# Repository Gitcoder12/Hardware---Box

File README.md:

Hardware-Box

Universal Hardware Configuration, Cloning & Replication Platform

A comprehensive library of hardware and PCB configurations, with cloning, duplication, and replication capabilities using 3D printers and other suitable manufacturing technologies.

---

Overview

Hardware-Box aims to create a centralized ecosystem for documenting, analyzing, reconstructing, and replicating physical hardware.

The platform will organize hardware configurations, PCB layouts, electronic components, mechanical structures, CAD models, firmware documentation, and manufacturing specifications.

The long-term vision is to make hardware designs easier to understand, reproduce, modify, and manufacture.

Core Capabilities

- Hardware Database: Organized configurations for phones, televisions, computers, appliances, and electronic devices.
- PCB Library: Circuit board layouts, schematics, component placements, and board specifications.
- Hardware Cloning: Reconstruct compatible hardware designs from verified documentation and authorized reference devices.
- 3D Replication: Generate and reproduce compatible physical components using 3D printing.
- CAD Integration: Store and process STEP, STL, 3MF, and other supported design formats.
- Component Library: Catalog electronic and mechanical components with specifications.
- Manufacturing Support: Document suitable fabrication technologies, materials, tolerances, and assembly procedures.
- Compatibility Analysis: Compare hardware configurations and identify compatible replacement components.

Supported Hardware Categories

Category| Examples
Mobile Devices| Smartphones, tablets
Entertainment| Televisions, remotes, speakers
Computing| Laptops, desktops, accessories
Electronics| PCBs, embedded systems, controllers
Mechanical| Enclosures, brackets, connectors
Appliances| Electronic and mechanical components

Replication Technologies

- FDM / FFF 3D printing
- SLA / Resin printing
- SLS printing
- CNC machining
- PCB manufacturing
- Laser cutting
- Other suitable fabrication technologies

Not every component can be reproduced using 3D printing. Electronic chips, displays, sensors, and specialized components may require separate manufacturing or sourcing.

Planned Architecture

Hardware-Box/
│
├── database/
│   ├── devices/
│   ├── configurations/
│   └── manufacturers/
│
├── pcb/
│   ├── layouts/
│   ├── schematics/
│   └── components/
│
├── designs/
│   ├── cad/
│   ├── 3d-models/
│   └── mechanical/
│
├── fabrication/
│   ├── materials/
│   ├── printers/
│   └── manufacturing/
│
├── tools/
│   ├── analyzers/
│   ├── converters/
│   └── validators/
│
├── docs/
├── examples/
└── tests/

Technology Direction

- Python for automation and hardware processing
- JSON for structured device configurations
- KiCad for PCB design and documentation
- FreeCAD for parametric CAD workflows
- Open-source 3D printing and manufacturing tools
- Future web interface for browsing and managing hardware designs

Development Roadmap

- [ ] Establish repository architecture
- [ ] Define universal hardware configuration schema
- [ ] Build device and component database
- [ ] Support PCB design documentation
- [ ] Integrate CAD model storage and validation
- [ ] Develop hardware comparison tools
- [ ] Build 3D model preparation workflows
- [ ] Introduce replication and fabrication pipelines
- [ ] Develop a searchable hardware catalog
- [ ] Build a unified web interface

Design Principles

- Open documentation and interoperability
- Reproducible and verifiable configurations
- Modular and extensible architecture
- Accurate technical specifications
- Responsible and authorized hardware replication
- Respect for intellectual property and device security

Project Status

Early Development — Architecture and Planning

Hardware-Box is currently in its initial planning stage. Features and integrations will be implemented incrementally.

Contributing

Contributions involving hardware documentation, open designs, component specifications, CAD models, PCB layouts, and manufacturing workflows are welcome.

All submitted assets must have appropriate licensing and provenance information.

License

Software is licensed under Apache License 2.0.

Individual hardware designs, CAD assets, and documentation may use separate explicitly stated licenses.

---

Hardware-Box

Document. Analyze. Reconstruct. Replicate. Manufacture.

---

## AI-maintained project notes (secondary — 2026-11-13)

This section supplements the maintainer-authored README above. The original text has been restored verbatim from Git-history baseline `46f34793b14171dbe76eea0be68a4bfb9a891d74`; this addendum does not replace or certify the original claims.

- The current source tree, runtime data and tests are the implementation source of truth. Roadmap items, draft PRs and AI-generated descriptions are not shipped features by themselves.
- Preserve real and maintainer-provided data. Never silently substitute generated or placeholder data. Clearly label and isolate synthetic fixtures.
- Mark unverified sources, identifiers, metrics, benchmark results and external claims as unknown/unverified rather than guessing.
- Verify setup, execution, tests and public claims against the exact current commit before using this repository in a job, research or academic application.
- See [MODEL_AUDIT_ROUTER.md](MODEL_AUDIT_ROUTER.md) for independent model review instructions and the merge gate.

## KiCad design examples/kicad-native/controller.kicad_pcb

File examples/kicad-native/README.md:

# Native KiCad sample project

These compact `.kicad_sch` and `.kicad_pcb` files are deliberately small parser fixtures for Hardware-Box. They demonstrate the file structures inspected by `inspect-kicad`; they are not a complete manufacturable circuit design and have not been validated by KiCad ERC/DRC.

Run from the repository root:

```bash
hardware-box inspect-kicad examples/kicad-native/controller.kicad_sch
hardware-box inspect-kicad examples/kicad-native/controller.kicad_pcb
hardware-box audit-kicad examples/kicad/bom.csv examples/kicad/netlist.xml \\
  --schematic examples/kicad-native/controller.kicad_sch \\
  --pcb examples/kicad-native/controller.kicad_pcb
```

The audit uses reference-inventory consistency, not full netlist-to-PCB equivalence.

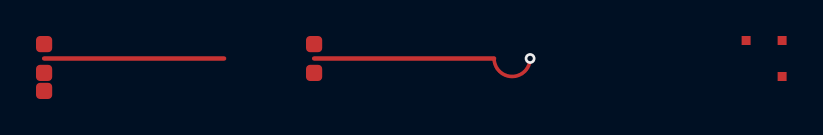
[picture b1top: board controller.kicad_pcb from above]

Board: 2 copper layers, 3 parts (0 on the bottom side), 3 nets.

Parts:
C1: 100nF; C_0603
R1: 10k; R_0603
U1: MCU; QFN-32

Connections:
3V3: C1.2, R1.2, U1.4
GND: C1.1, R1.1, U1.3
UART_TX: R1.3, U1.8
